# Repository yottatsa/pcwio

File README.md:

# Amstrad PCW8256 / PCW8512 IO Card
Modern *CPS8256*/*SCA Mk2* Interface

Based on:

* [jamesots/pcw_serial_board](https://github.com/jamesots/pcw_serial_board),
* `uSIO`,
* reverse-engineered [`TIME.MAC`](http://www.seasip.info/Cpm/2000/time.mac) from *SCA Mk2* by John Elliott.

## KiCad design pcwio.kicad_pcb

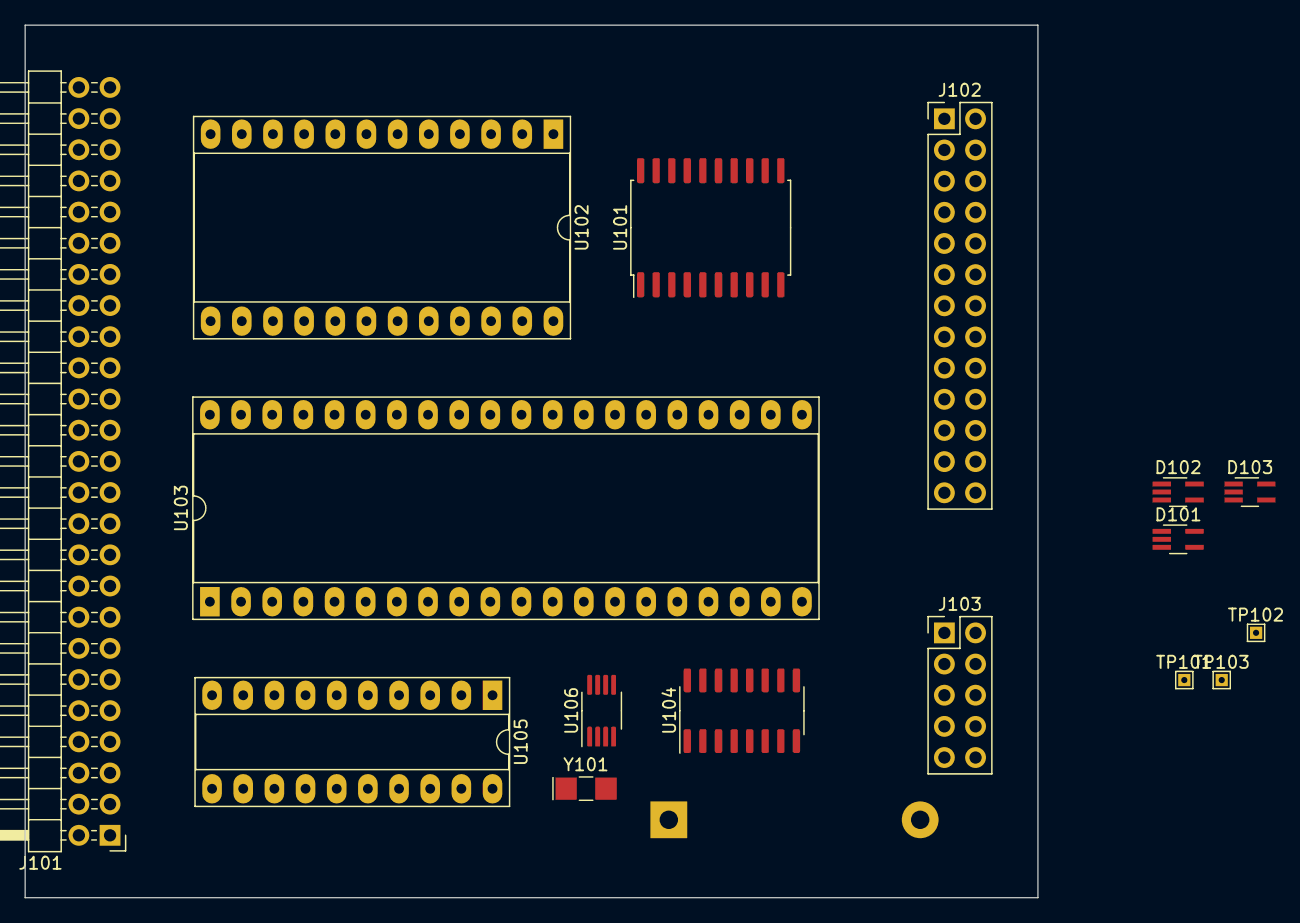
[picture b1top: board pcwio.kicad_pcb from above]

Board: 2 copper layers, 82.5 x 71.1 mm, 17 parts (1 on the bottom side), 59 nets, no tracks yet.

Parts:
BT101: RTC Battery; BatteryHolder_Keystone_106_1x20mm
D101, D102, D103: PESD5V0L4UG; SOT-353_SC-70-5_Handsoldering
J101: PCW/Z80 Expansion port; PinHeader_2x25_P2.54mm_Horizontal
J102: DB25_Female; PinHeader_2x13_P2.54mm_Vertical
J103: DB9; PinHeader_2x05_P2.54mm_Vertical
TP101, TP102, TP103: TestPoint_Probe; TestPoint_THTPad_1.0x1.0mm_Drill0.5mm
U101: 74LS573; SOIC-20W_7.5x12.8mm_P1.27mm
U102: 8254; DIP-24_W15.24mm_Socket_LongPads
U103: Z80DART; DIP-40_W15.24mm_Socket_LongPads
U104: MAX232; SOIC-16_3.9x9.9mm_P1.27mm
U105: GAL16V8; DIP-20_W7.62mm_Socket_LongPads
U106: DS1307; MSOP-8_3x3mm_P0.65mm
Y101: 32.768kHz; Crystal_SMD_EuroQuartz_EQ161-2Pin_3.2x1.5mm_HandSoldering

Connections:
5VDC: D103.5 (K4), J101.5, J101.6, U101.20 (VCC), U102.11 (GATE0), U102.14 (GATE1), U102.16 (GATE2), U102.24 (VCC), U103.6 (IEI), U103.9 (VCC), U103.28 (RXDB), U104.16 (VCC), U105.20 (VCC), U106.8 (VCC)
A0: J101.23, U102.19 (A0), U103.33 (C/~D)
A1: J101.24, U102.20 (A1), U103.34 (B/~A)
A2: J101.21, U105.4 (I4)
A3: J101.22, U105.5 (I5)
A4: J101.19, U105.6 (I6)
A5: J101.20, U105.7 (I7)
A6: J101.17, U105.8 (I8)
A7: J101.18, U105.9 (I9)
CEN.D0: D101.1 (K1), J102.2, U101.19 (Q0)
CEN.D1: D101.3 (K2), J102.3, U101.18 (Q1)
CEN.D2: D101.4 (K3), J102.4, U101.17 (Q2)
CEN.D3: D101.5 (K4), J102.5, U101.16 (Q3)
CEN.D4: D102.1 (K1), J102.6, U101.15 (Q4)
CEN.D5: D102.3 (K2), J102.7, U101.14 (Q5)
CEN.D6: D102.4 (K3), J102.8, U101.13 (Q6)
CEN.D7: D102.5 (K4), J102.9, U101.12 (Q7)
CEN.PAPEROUT: D103.4 (K3), J102.12
CEN.~BUSY: D103.1 (K1), J102.11
CEN.~STROBE: D103.3 (K2), J102.1, U105.18 (IO2)
CLK: J101.48, U105.1 (I1/CLK)
D0: J101.31, U101.2 (D0), U102.8 (D0), U103.40 (D0)
D1: J101.32, U101.3 (D1), U102.7 (D1), U103.1 (D1)
D2: J101.29, U101.4 (D2), U102.6 (D2), U103.39 (D2)
D3: J101.30, U101.5 (D3), U102.5 (D3), U103.2 (D3)
D4: J101.27, U101.6 (D4), U102.4 (D4), U103.38 (D4)
D5: J101.28, U101.7 (D5), U102.3 (D5), U103.3 (D5)
D6: J101.25, U101.8 (D6), U102.2 (D6), U103.37 (D6)
D7: J101.26, U101.9 (D7), U102.1 (D7), U103.4 (D7)
DART.CLK: U103.20 (CLK), U105.12 (IO8)
DART.~CS: U103.35 (~CE), U105.16 (IO4)
EXT.~SDI: TP101.1, U103.29 (~RIB)
EXT.~SDO: TP102.1, U103.24 (~RTSB)
GND: BT101.2 (-), D101.2 (A), D102.2 (A), D103.2 (A), J101.3, J101.4, J101.49, J101.50, J102.18, J102.19, J102.20, J102.21, J102.22, J102.23, J102.24, J102.25, J103.5, U101.1 (OE), U101.10 (GND), U102.12 (GND), U103.31 (GND), U104.15 (GND), U105.10 (GND), U105.11 (I10/~OE), U106.4 (GND)
unnamed: U106.1 (X1), Y101.1
unnamed: U106.2 (X2), Y101.2
PAR.WR: U101.11 (Load), U105.15 (IO5)
PAR.~STROBE: U103.25 (~DTRB), U105.2 (I2)
RS232.CTS: J103.8, U104.8 (R2IN)
RS232.RTS: J103.7, U104.7 (T2OUT)
RS232.RXD: J103.2, U104.13 (R1IN)
RS232.TXD: J103.3, U104.14 (T1OUT)
RTC.~SCL: TP103.1, U103.16 (~DTRA), U106.6 (SCL)
SERIAL.CTS: U103.18 (~CTSA), U104.9 (R2OUT)
SERIAL.RTS: U103.17 (~RTSA), U104.10 (T2IN)
SERIAL.RXD: U103.12 (RxDA), U104.12 (R1OUT)
SERIAL.TXD: U103.15 (TxDA), U104.11 (T1IN)
TIMER.CLK: U102.9 (CLK0), U102.15 (CLK1), U102.18 (CLK2), U105.19 (IO1)
TIMER.~CS: U102.21 (~CS), U105.17 (I03)
VBAT: BT101.1 (+), U106.3 (VBAT)
~INT: J101.36, U103.5 (~INT)
~IOREQ: J101.42, U103.36 (~IORQ), U105.3 (I3)
~M1: J101.34, U103.8 (~M1)
~RD: J101.41, U102.22 (~RD), U103.32 (~RD)
~RESET: J101.33, U103.21 (~RESET)
~RxCA: U102.13 (OUT1), U103.13 (~RxCA)
~RxTxCB: U102.17 (OUT2), U103.27 (~RxTxCB)
~TxCA: U102.10 (OUT0), U103.14 (~TxCA)
~WR: J101.39, U102.23 (~WR)

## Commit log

2023-07-04 initial
